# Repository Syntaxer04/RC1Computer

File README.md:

# RC1Computer
8-Bit Relay Computer inspired by Harry Porter and DipDot
# General Information
This Computer, inspired Harry H Porter III, Ph.D, Paul Law, and Youtuber DipDot, is (almost) completly made out of relays, 607 of them to be exact.

# Specifications
- 32 kb RAM
- It has ~11~ 15 8 Bit Registers. Some of them can also funtcion as 16 Bit Registers.
- A clock rate Between 3 and 8 Hertz
- 8 Bit Data and Instruction Bus, as well as an 16* Bit Adress Bus
<sub>*only 15 bits are actually used, but the 16th Bit is still usable for other Peripherals/More Memeory</sub>

# Changes in V0.2
- Changed how I managed the Bus on the RC-1. The Bus Board now encompasses all Register Signals and otherwise, except for the Timing pulses, which is only used by the Controller.
- Caught most the Routing mistakes I made in the first Version. The second run really helped spotting obvious and not so obvious mistakes.
- Added a board for the front panel functions. The switches are not mounted on the Board however, and so are the LEDs.
- I also started experimenting with Capacitor Storage. I included my initial design in this version.
- The memory board had an overhaul, with more isolation and better logic.
- The ALU has been split into two boards. I was able to do this because of the new backplane.

# Future features
- ~I want to make some sort Storage medium. A Tape interface, similar to DipDot's design, would be nice, although for a computer like that kind of lame in my opinion. I am thinking more like a paper based interface, like the one Usagi electric build for the [UE1](https://www.youtube.com/playlist?list=PLnw98JPyObn0v-98gRV9PfzAQONTKxql3). One Slight Problem thogh: _Reading_ may be somewhat easy, the _writing_ on the other hand may be a little challenge... We'll burn that bridge when we get there.~
- Tape Loader has been added, function not Tested however.
- The Second thing i want to make for this project is some sort of Serial/ Terminal output. That itself is not that hard all things considered, it's nearly a chip solution. The real problem is that the Computer most likely lacks any sort of speed for that kind of outpu. So i either have to buffer the output, make it _exceptionaly_ slow, or find some other way of sending a serial signal of of the Computer.

# Links
[Paul Law´s Youtube channel](https://www.youtube.com/@paul80nd), and his [personal Blog](https://www.relaycomputer.co.uk/).
[Harry Porter´s Webiste](https://web.cecs.pdx.edu/~harry/Relay/index.html), specifically, [this PDF](https://web.cecs.pdx.edu/~harry/Relay/RelayPaper.pdf).
Lastly, [DipDot´s Youtube channel](https://www.youtube.com/@dipdoting). He was the main inspiration for this project and his videos are well made.

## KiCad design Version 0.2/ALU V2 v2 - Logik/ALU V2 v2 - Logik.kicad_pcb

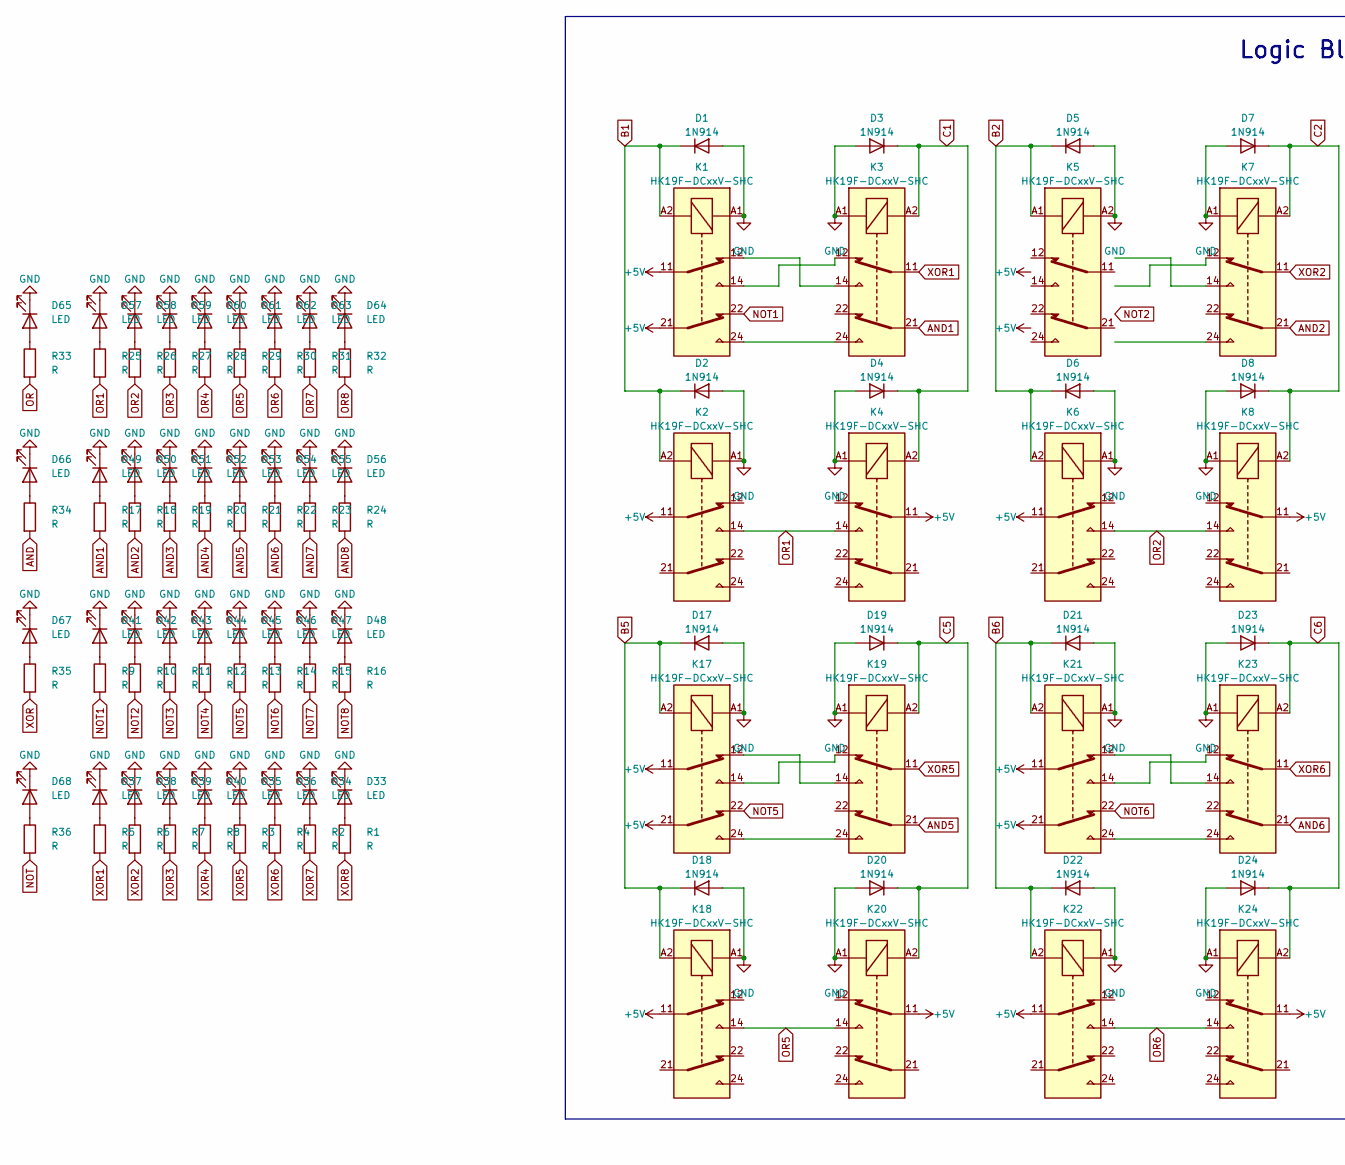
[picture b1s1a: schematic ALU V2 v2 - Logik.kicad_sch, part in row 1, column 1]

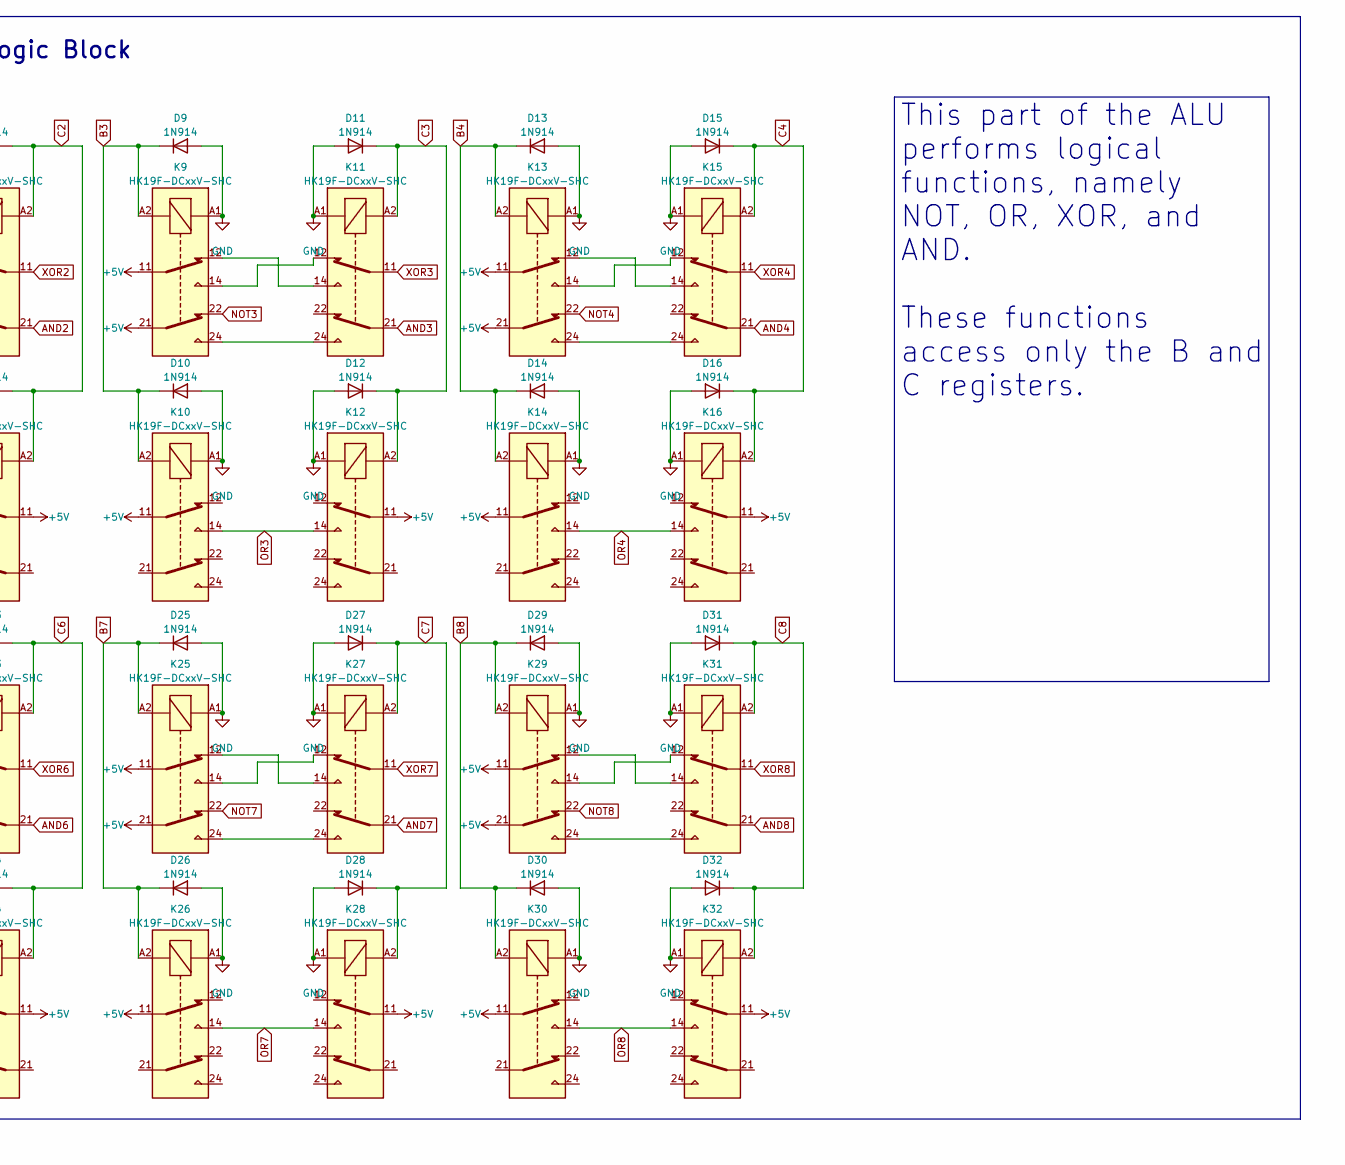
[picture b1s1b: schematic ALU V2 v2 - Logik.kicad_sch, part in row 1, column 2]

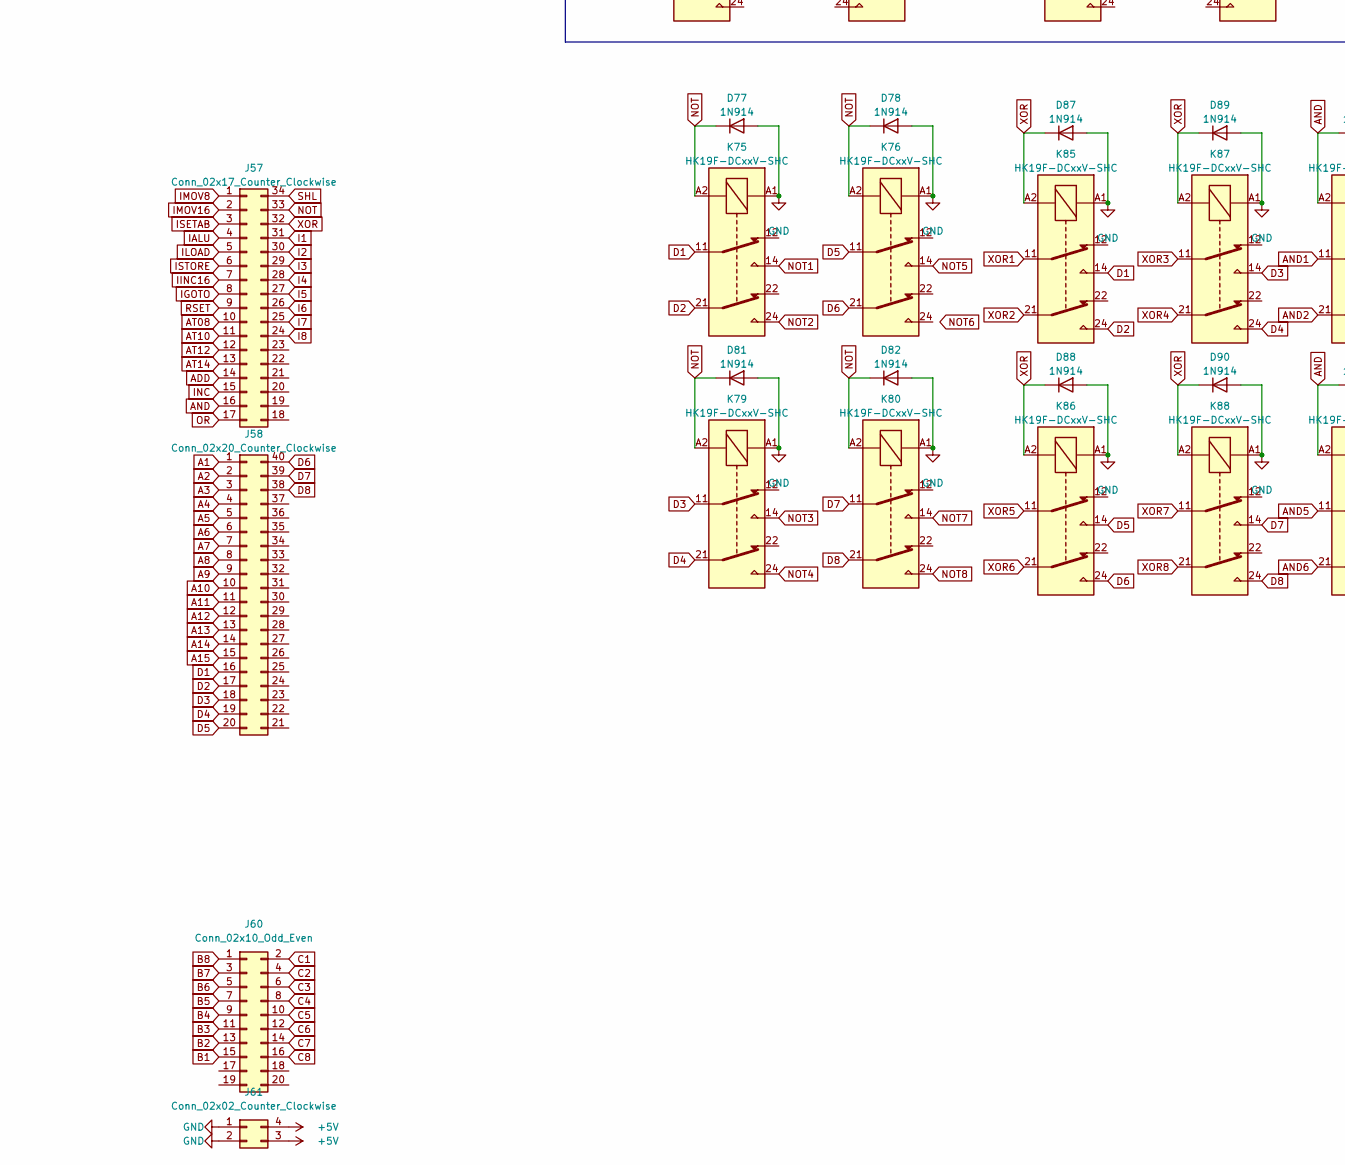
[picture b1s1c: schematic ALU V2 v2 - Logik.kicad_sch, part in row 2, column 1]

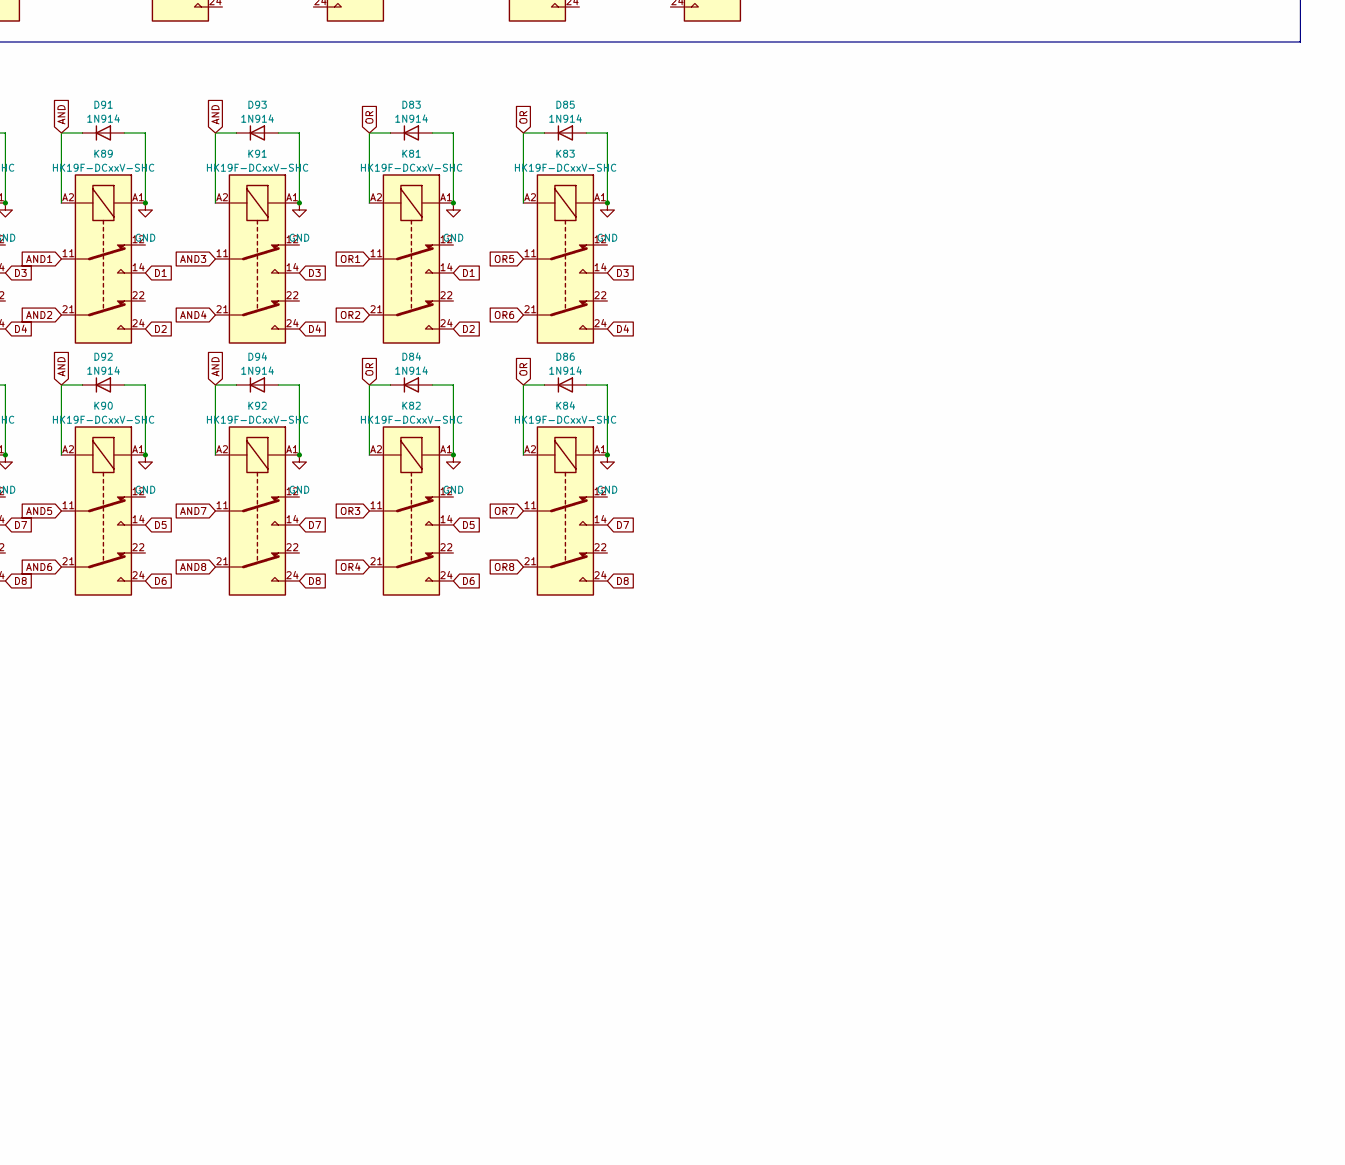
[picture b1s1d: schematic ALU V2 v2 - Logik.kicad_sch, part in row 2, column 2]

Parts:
D1, D2, D3, D4, D5, D6, D7, D8, D9, D10, D11, D12, D13, D14, D15, D16, D17, D18, D19, D20, D21, D22, D23, D24, D25, D26, D27, D28, D29, D30, D31, D32, D77, D78, D81, D82, D83, D84, D85, D86, D87, D88, D89, D90, D91, D92, D93, D94: 1N914; D_DO-35_SOD27_P7.62mm_Horizontal
D33, D34, D35, D36, D37, D38, D39, D40, D41, D42, D43, D44, D45, D46, D47, D48, D49, D50, D51, D52, D53, D54, D55, D56, D57, D58, D59, D60, D61, D62, D63, D64, D65, D66, D67, D68: LED; LED_D5.0mm
J57: Conn_02x17_Counter_Clockwise; PinSocket_2x17_P2.54mm_Horizontal
J58: Conn_02x20_Counter_Clockwise; PinSocket_2x20_P2.54mm_Horizontal
J60: Conn_02x10_Odd_Even; PinSocket_2x10_P2.54mm_Horizontal
J61: Conn_02x02_Counter_Clockwise; PinSocket_2x02_P2.54mm_Horizontal
K1, K2, K3, K4, K5, K6, K7, K8, K9, K10, K11, K12, K13, K14, K15, K16, K17, K18, K19, K20, K21, K22, K23, K24, K25, K26, K27, K28, K29, K30, K31, K32, K75, K76, K79, K80, K81, K82, K83, K84, K85, K86, K87, K88, K89, K90, K91, K92: HK19F-DCxxV-SHC; Relay_DPDT_Finder_30.22
R1, R2, R3, R4, R5, R6, R7, R8, R9, R10, R11, R12, R13, R14, R15, R16, R17, R18, R19, R20, R21, R22, R23, R24, R25, R26, R27, R28, R29, R30, R31, R32, R33, R34, R35, R36: R; R_Axial_DIN0309_L9.0mm_D3.2mm_P12.70mm_Horizontal

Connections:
+5V: J61.3, J61.4, K1.11, K1.21, K2.11, K4.11, K5.11, K5.21, K6.11, K8.11, K9.11, K9.21, K10.11, K12.11, K13.11, K13.21, K14.11, K16.11, K17.11, K17.21, K18.11, K20.11, K21.11, K21.21, K22.11, K24.11, K25.11, K25.21, K26.11, K28.11, K29.11, K29.21, K30.11, K32.11
A1: J58.1
A2: J58.2
A3: J58.3
A4: J58.4
A5: J58.5
A6: J58.6
A7: J58.7
A8: J58.8
A9: J58.9
A10: J58.10
A11: J58.11
A12: J58.12
A13: J58.13
A14: J58.14
A15: J58.15
ADD: J57.14
AND: D91.1 (K), D92.1 (K), D93.1 (K), D94.1 (K), J57.16, K89.A2, K90.A2, K91.A2, K92.A2, R34.2
AND1: K3.21, K89.11, R17.2
AND2: K7.21, K89.21, R18.2
AND3: K11.21, K91.11, R19.2
AND4: K15.21, K91.21, R20.2
AND5: K19.21, K90.11, R21.2
AND6: K23.21, K90.21, R22.2
AND7: K27.21, K92.11, R23.2
AND8: K31.21, K92.21, R24.2
AT08: J57.10
AT10: J57.11
AT12: J57.12
AT14: J57.13
B1: D1.1 (K), D2.1 (K), J60.15, K1.A2, K2.A2
B3: D9.1 (K), D10.1 (K), J60.11, K9.A2, K10.A2
B4: D13.1 (K), D14.1 (K), J60.9, K13.A2, K14.A2
B5: D17.1 (K), D18.1 (K), J60.7, K17.A2, K18.A2
B6: D21.1 (K), D22.1 (K), J60.5, K21.A2, K22.A2
B7: D25.1 (K), D26.1 (K), J60.3, K25.A2, K26.A2
B8: D29.1 (K), D30.1 (K), J60.1, K29.A2, K30.A2
C1: D3.1 (K), D4.1 (K), J60.2, K3.A2, K4.A2
C2: D7.1 (K), D8.1 (K), J60.4, K7.A2, K8.A2
C3: D11.1 (K), D12.1 (K), J60.6, K11.A2, K12.A2
C4: D15.1 (K), D16.1 (K), J60.8, K15.A2, K16.A2
C5: D19.1 (K), D20.1 (K), J60.10, K19.A2, K20.A2
C6: D23.1 (K), D24.1 (K), J60.12, K23.A2, K24.A2
C7: D27.1 (K), D28.1 (K), J60.14, K27.A2, K28.A2
C8: D31.1 (K), D32.1 (K), J60.16, K31.A2, K32.A2
D1: J58.16, K75.11, K81.14, K85.14, K89.14
D2: J58.17, K75.21, K81.24, K85.24, K89.24
D3: J58.18, K79.11, K83.14, K87.14, K91.14
D4: J58.19, K79.21, K83.24, K87.24, K91.24
D5: J58.20, K76.11, K82.14, K86.14, K90.14
D6: J58.40, K76.21, K82.24, K86.24, K90.24
D7: J58.39, K80.11, K84.14, K88.14, K92.14
D8: J58.38, K80.21, K84.24, K88.24, K92.24
I1: J57.31
I2: J57.30
I3: J57.29
I4: J57.28
I5: J57.27
I6: J57.26
I7: J57.25
I8: J57.24
IALU: J57.4
IGOTO: J57.8
IINC16: J57.7
ILOAD: J57.5
IMOV8: J57.1
IMOV16: J57.2
INC: J57.15
ISETAB: J57.3
ISTORE: J57.6
NOT: D77.1 (K), D78.1 (K), D81.1 (K), D82.1 (K), J57.33, K75.A2, K76.A2, K79.A2, K80.A2, R36.2
NOT1: K1.22, K75.14, R9.2
NOT2: K5.22, K75.24, R10.2
NOT3: K9.22, K79.14, R11.2
NOT4: K13.22, K79.24, R12.2
NOT5: K17.22, K76.14, R13.2
NOT6: K21.22, R14.2
NOT7: K25.22, K80.14, R15.2
NOT8: K29.22, K80.24, R16.2
unnamed: D33.2 (A), R1.1
unnamed: D34.2 (A), R2.1
unnamed: D35.2 (A), R3.1
unnamed: D36.2 (A), R4.1
unnamed: D37.2 (A), R5.1
unnamed: D38.2 (A), R6.1
unnamed: D39.2 (A), R7.1
unnamed: D40.2 (A), R8.1
unnamed: D41.2 (A), R9.1
unnamed: D42.2 (A), R10.1
unnamed: D43.2 (A), R11.1
unnamed: D44.2 (A), R12.1
unnamed: D45.2 (A), R13.1
unnamed: D46.2 (A), R14.1
unnamed: D47.2 (A), R15.1
unnamed: D48.2 (A), R16.1
unnamed: D49.2 (A), R17.1
unnamed: D50.2 (A), R18.1
unnamed: D51.2 (A), R19.1
unnamed: D52.2 (A), R20.1
unnamed: D53.2 (A), R21.1
unnamed: D54.2 (A), R22.1
unnamed: D55.2 (A), R23.1
unnamed: D56.2 (A), R24.1
unnamed: D57.2 (A), R25.1
unnamed: D58.2 (A), R26.1
unnamed: D59.2 (A), R27.1
unnamed: D60.2 (A), R28.1
unnamed: D61.2 (A), R29.1
unnamed: D62.2 (A), R30.1
unnamed: D63.2 (A), R31.1
unnamed: D64.2 (A), R32.1
unnamed: D65.2 (A), R33.1
unnamed: D66.2 (A), R34.1
unnamed: D67.2 (A), R35.1
unnamed: D68.2 (A), R36.1
unnamed: K1.12, K3.14
unnamed: K1.14, K3.12
unnamed: K1.24, K3.24
unnamed: K5.12, K7.14
unnamed: K5.14, K7.12
unnamed: K5.24, K7.24
unnamed: K9.14, K11.12
unnamed: K9.12, K11.14
unnamed: K9.24, K11.24
unnamed: K13.12, K15.14
unnamed: K13.14, K15.12
unnamed: K13.24, K15.24
unnamed: K17.12, K19.14
unnamed: K17.14, K19.12
unnamed: K17.24, K19.24
unnamed: K21.12, K23.14
unnamed: K21.14, K23.12
unnamed: K21.24, K23.24
unnamed: K25.12, K27.14
unnamed: K25.14, K27.12
unnamed: K25.24, K27.24
unnamed: K29.12, K31.14
unnamed: K29.14, K31.12
unnamed: K29.24, K31.24
OR: D83.1 (K), D84.1 (K), D85.1 (K), D86.1 (K), J57.17, K81.A2, K82.A2, K83.A2, K84.A2, R33.2
OR1: K2.14, K4.14, K81.11, R25.2
OR2: K6.14, K8.14, K81.21, R26.2
OR3: K10.14, K12.14, K82.11, R27.2
OR4: K14.14, K16.14, K82.21, R28.2
OR5: K18.14, K20.14, K83.11, R29.2
OR6: K22.14, K24.14, K83.21, R30.2
OR7: K26.14, K28.14, K84.11, R31.2
OR8: K30.14, K32.14, K84.21, R32.2
RSET: J57.9
SHL: J57.34
XOR: D87.1 (K), D88.1 (K), D89.1 (K), D90.1 (K), J57.32, K85.A2, K86.A2, K87.A2, K88.A2, R35.2
XOR1: K3.11, K85.11, R5.2
XOR2: K7.11, K85.21, R6.2
XOR3: K11.11, K87.11, R7.2
XOR4: K15.11, K87.21, R8.2
XOR5: K19.11, K86.11, R3.2
XOR6: K23.11, K86.21, R4.2
XOR7: K27.11, K88.11, R2.2
XOR8: K31.11, K88.21, R1.2

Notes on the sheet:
Logic Block
This part of the ALU performs logical functions, namely NOT, OR, XOR, and AND. These functions access only the B and C registers.

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
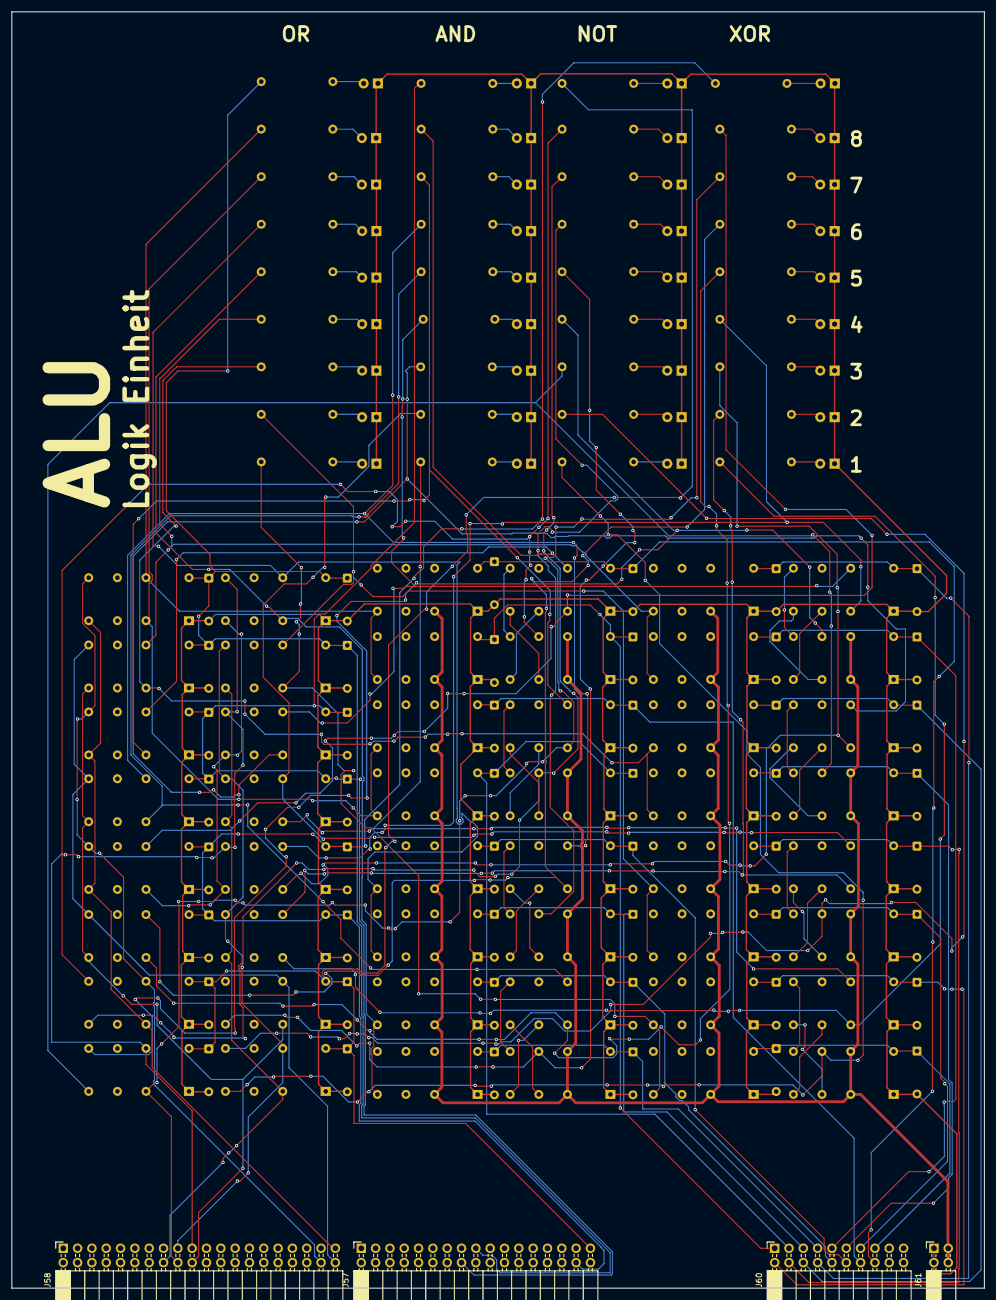
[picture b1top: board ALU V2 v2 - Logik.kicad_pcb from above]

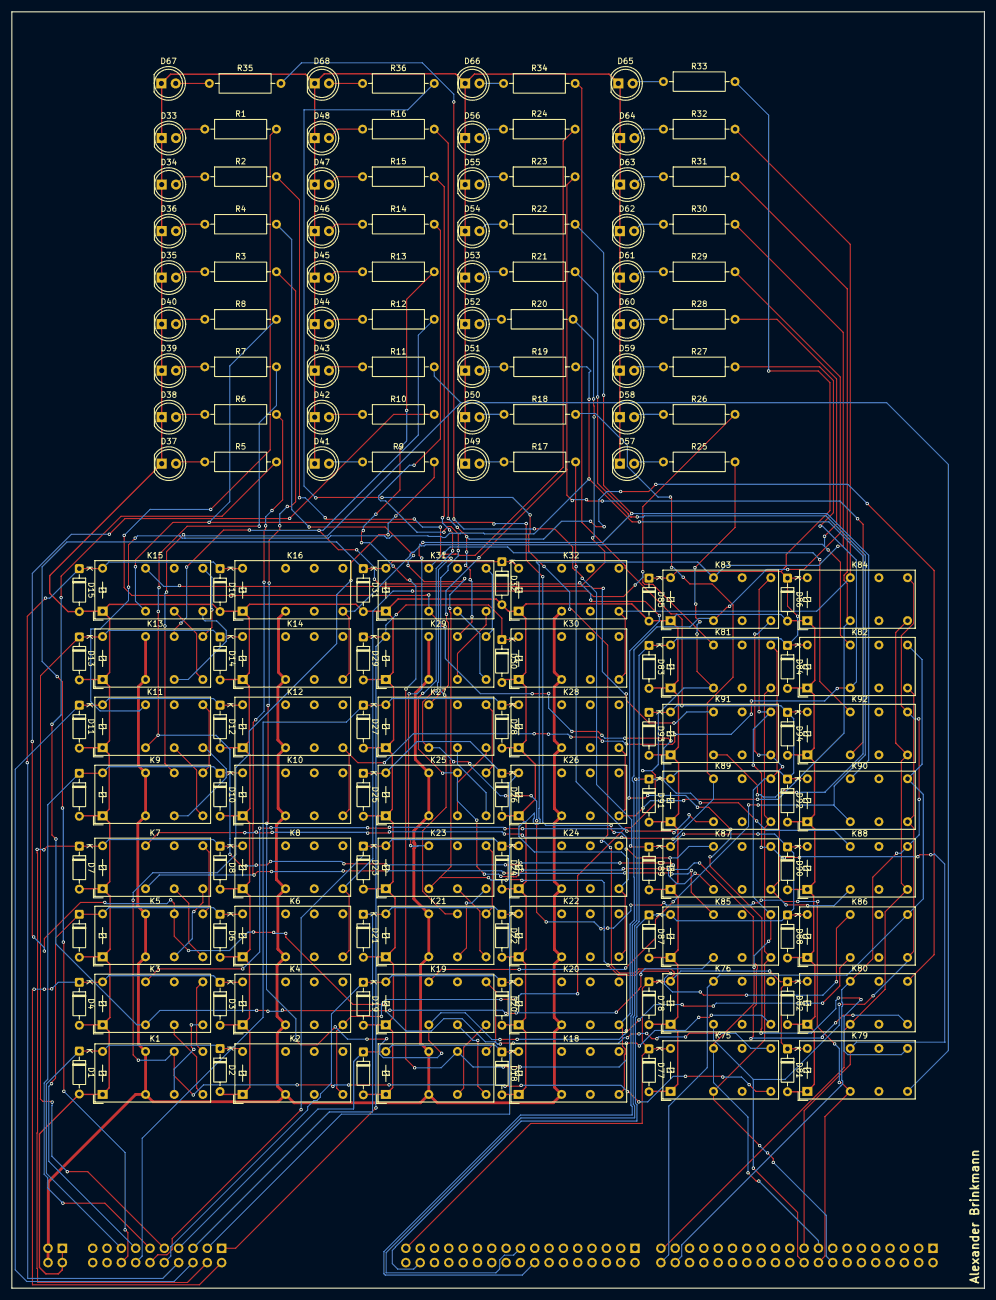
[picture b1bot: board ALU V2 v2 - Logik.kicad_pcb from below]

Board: 2 copper layers, 172.5 x 226.3 mm, 172 parts (168 on the bottom side), 122 nets.

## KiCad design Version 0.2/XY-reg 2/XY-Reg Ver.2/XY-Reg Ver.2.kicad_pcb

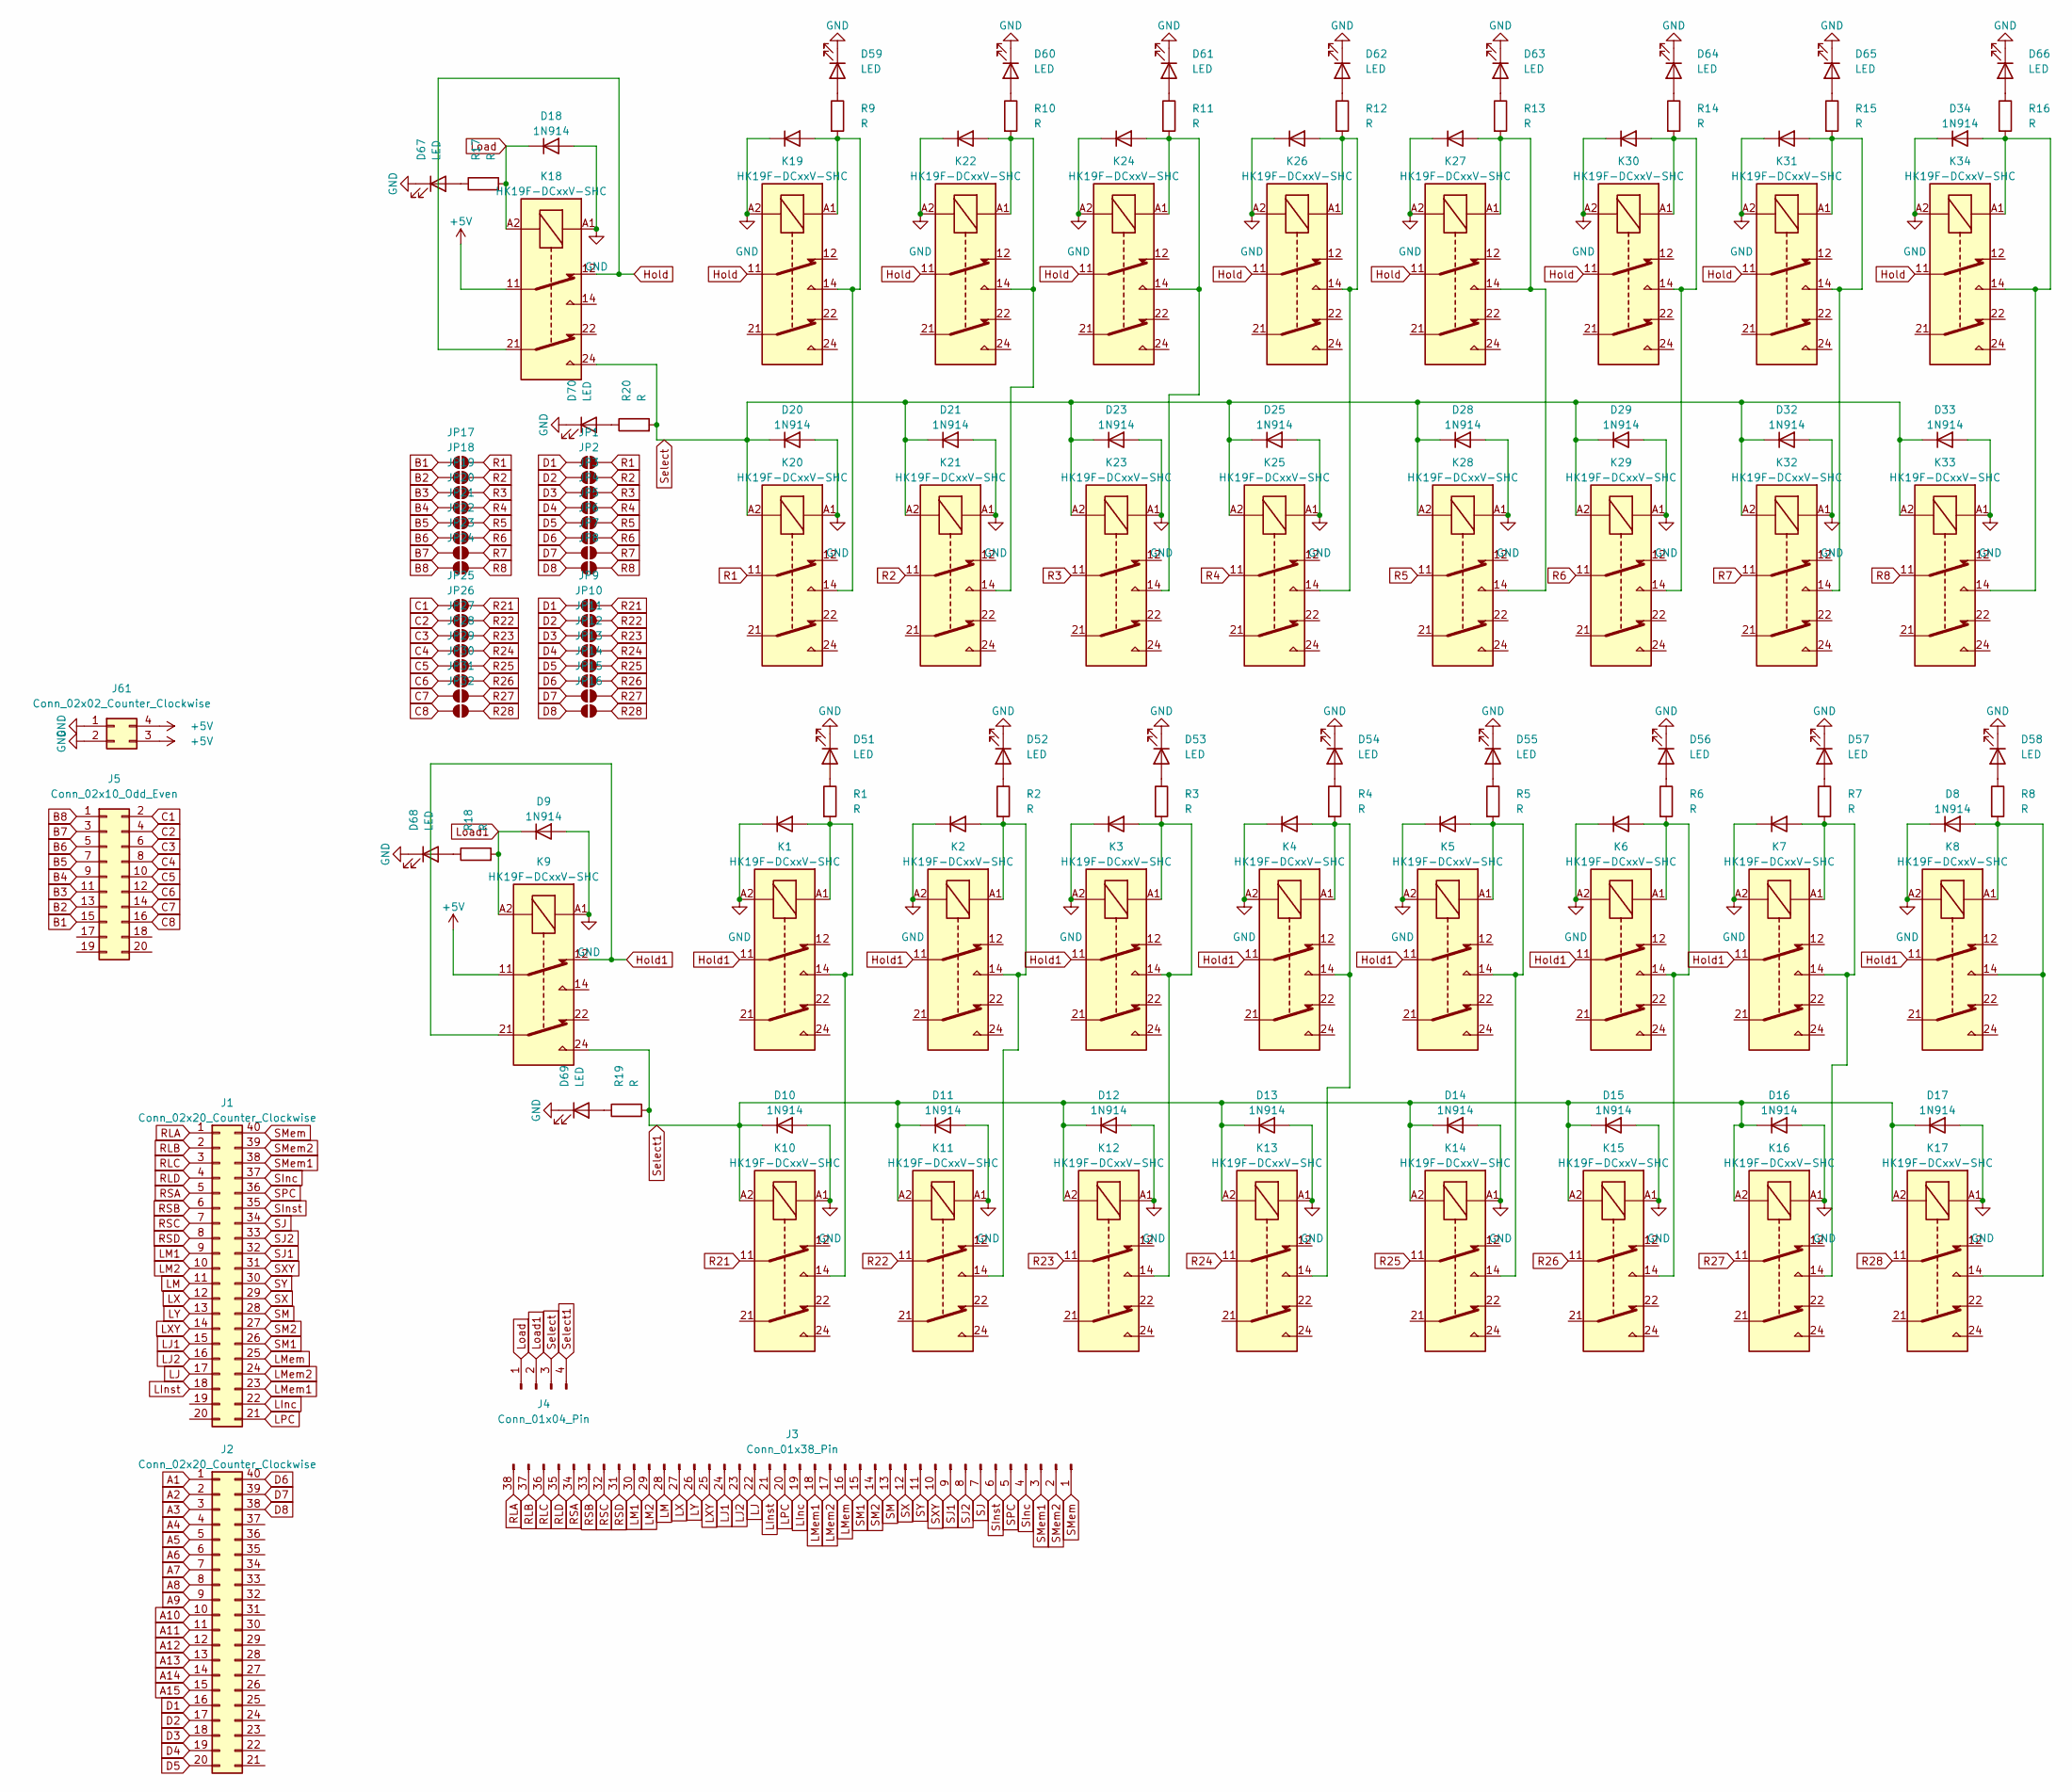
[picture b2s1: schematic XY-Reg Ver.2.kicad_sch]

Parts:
D1, D2, D3, D4, D5, D6, D7, D8, D9, D10, D11, D12, D13, D14, D15, D16, D17, D18, D19, D20, D21, D22, D23, D24, D25, D26, D27, D28, D29, D30, D31, D32, D33, D34: 1N914; D_DO-35_SOD27_P7.62mm_Horizontal
D51, D52, D53, D54, D55, D56, D57, D58, D59, D60, D61, D62, D63, D64, D65, D66, D67, D68, D70: LED; LED_D5.0mm ohne SilkS
D69: LED; LED_D5.0mm
J1, J2: Conn_02x20_Counter_Clockwise; PinSocket_2x20_P2.54mm_Horizontal
J3: Conn_01x38_Pin; PinHeader_1x38_P2.54mm_Vertical
J4: Conn_01x04_Pin; PinHeader_1x04_P2.54mm_Vertical
J5: Conn_02x10_Odd_Even; PinHeader_2x10_P2.54mm_Horizontal
J61: Conn_02x02_Counter_Clockwise; PinSocket_2x02_P2.54mm_Vertical
JP1, JP2, JP3, JP4, JP5, JP6, JP7, JP8, JP9, JP10, JP11, JP12, JP13, JP14, JP15, JP16, JP17, JP18, JP19, JP20, JP21, JP22, JP23, JP24, JP25, JP26, JP27, JP28, JP29, JP30, JP31, JP32: SolderJumper_2_Open; SolderJumper-2_P1.3mm_Open_Pad1.0x1.5mm
K1, K2, K3, K4, K5, K6, K7, K8, K9, K10, K11, K12, K13, K14, K15, K16, K17, K18, K19, K20, K21, K22, K23, K24, K25, K26, K27, K28, K29, K30, K31, K32, K33, K34: HK19F-DCxxV-SHC; Relay_DPDT_Finder_30.22 ohne SilkS
R1, R2, R3, R4, R5, R6, R7, R8, R9, R10, R11, R12, R13, R14, R15, R16, R17, R18, R19, R20: R; R_Axial_DIN0204_L3.6mm_D1.6mm_P7.62mm_Horizontal

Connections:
+5V: J61.3, J61.4, K9.11, K18.11
A1: J2.1
A2: J2.2
A3: J2.3
A4: J2.4
A5: J2.5
A6: J2.6
A7: J2.7
A8: J2.8
A9: J2.9
A10: J2.10
A11: J2.11
A12: J2.12
A13: J2.13
A14: J2.14
A15: J2.15
B1: J5.15, JP17.1 (A)
B2: J5.13, JP18.1 (A)
B3: J5.11, JP19.1 (A)
B4: J5.9, JP20.1 (A)
B5: J5.7, JP21.1 (A)
B6: J5.5, JP22.1 (A)
B7: J5.3, JP23.1 (A)
B8: J5.1, JP24.1 (A)
C1: J5.2, JP25.1 (A)
C2: J5.4, JP26.1 (A)
C3: J5.6, JP27.1 (A)
C4: J5.8, JP28.1 (A)
C5: J5.10, JP29.1 (A)
C6: J5.12, JP30.1 (A)
C7: J5.14, JP31.1 (A)
C8: J5.16, JP32.1 (A)
D1: J2.16, JP1.1 (A), JP9.1 (A)
D2: J2.17, JP2.1 (A), JP10.1 (A)
D3: J2.18, JP3.1 (A), JP11.1 (A)
D4: J2.19, JP4.1 (A), JP12.1 (A)
D5: J2.20, JP5.1 (A), JP13.1 (A)
D6: J2.40, JP6.1 (A), JP14.1 (A)
D7: J2.39, JP7.1 (A), JP15.1 (A)
D8: J2.38, JP8.1 (A), JP16.1 (A)
GND: D1.1 (K), D2.1 (K), D3.1 (K), D4.1 (K), D5.1 (K), D6.1 (K), D7.1 (K), D8.1 (K), D9.2 (A), D10.2 (A), D11.2 (A), D12.2 (A), D13.2 (A), D14.2 (A), D15.2 (A), D16.2 (A), D17.2 (A), D18.2 (A), D19.1 (K), D20.2 (A), D21.2 (A), D22.1 (K), D23.2 (A), D24.1 (K), D25.2 (A), D26.1 (K), D27.1 (K), D28.2 (A), D29.2 (A), D30.1 (K), D31.1 (K), D32.2 (A), D33.2 (A), D34.1 (K), D51.1 (K), D52.1 (K), D53.1 (K), D54.1 (K), D55.1 (K), D56.1 (K), D57.1 (K), D58.1 (K), D59.1 (K), D60.1 (K), D61.1 (K), D62.1 (K), D63.1 (K), D64.1 (K), D65.1 (K), D66.1 (K), D67.1 (K), D68.1 (K), D69.1 (K), D70.1 (K), J61.1, J61.2, K1.A2, K2.A2, K3.A2, K4.A2, K5.A2, K6.A2, K7.A2, K8.A2, K9.A1, K10.A1, K11.A1, K12.A1, K13.A1, K14.A1, K15.A1, K16.A1, K17.A1, K18.A1, K19.A2, K20.A1, K21.A1, K22.A2, K23.A1, K24.A2, K25.A1, K26.A2, K27.A2, K28.A1, K29.A1, K30.A2, K31.A2, K32.A1, K33.A1, K34.A2
Hold: K18.12, K18.21, K19.11, K22.11, K24.11, K26.11, K27.11, K30.11, K31.11, K34.11
Hold1: K1.11, K2.11, K3.11, K4.11, K5.11, K6.11, K7.11, K8.11, K9.12, K9.21
LInc: J1.22, J3.19
LInst: J1.18, J3.21
LJ1: J1.15, J3.24
LJ2: J1.16, J3.23
LJ: J1.17, J3.22
LM: J1.11, J3.28
LM1: J1.9, J3.30
LM2: J1.10, J3.29
LMem: J1.25, J3.16
LMem1: J1.23, J3.18
LMem2: J1.24, J3.17
LPC: J1.21, J3.20
LX: J1.12, J3.27
LXY: J1.14, J3.25
LY: J1.13, J3.26
Load: D18.1 (K), J4.1, K18.A2, R17.2
Load1: D9.1 (K), J4.2, K9.A2, R18.2
unnamed: D1.2 (A), K1.14, K1.A1, K10.14, R1.2
unnamed: D2.2 (A), K2.14, K2.A1, K11.14, R2.2
unnamed: D3.2 (A), K3.14, K3.A1, K12.14, R3.2
unnamed: D4.2 (A), K4.14, K4.A1, K13.14, R4.2
unnamed: D5.2 (A), K5.14, K5.A1, K14.14, R5.2
unnamed: D6.2 (A), K6.14, K6.A1, K15.14, R6.2
unnamed: D7.2 (A), K7.14, K7.A1, K16.14, R7.2
unnamed: D8.2 (A), K8.14, K8.A1, K17.14, R8.2
unnamed: D19.2 (A), K19.14, K19.A1, K20.14, R9.2
unnamed: D22.2 (A), K21.14, K22.14, K22.A1, R10.2
unnamed: D24.2 (A), K23.14, K24.14, K24.A1, R11.2
unnamed: D26.2 (A), K25.14, K26.14, K26.A1, R12.2
unnamed: D27.2 (A), K27.14, K27.A1, K28.14, R13.2
unnamed: D30.2 (A), K29.14, K30.14, K30.A1, R14.2
unnamed: D31.2 (A), K31.14, K31.A1, K32.14, R15.2
unnamed: D34.2 (A), K33.14, K34.14, K34.A1, R16.2
unnamed: D51.2 (A), R1.1
unnamed: D52.2 (A), R2.1
unnamed: D53.2 (A), R3.1
unnamed: D54.2 (A), R4.1
unnamed: D55.2 (A), R5.1
unnamed: D56.2 (A), R6.1
unnamed: D57.2 (A), R7.1
unnamed: D58.2 (A), R8.1
unnamed: D59.2 (A), R9.1
unnamed: D60.2 (A), R10.1
unnamed: D61.2 (A), R11.1
unnamed: D62.2 (A), R12.1
unnamed: D63.2 (A), R13.1
unnamed: D64.2 (A), R14.1
unnamed: D65.2 (A), R15.1
unnamed: D66.2 (A), R16.1
unnamed: D67.2 (A), R17.1
unnamed: D68.2 (A), R18.1
unnamed: D69.2 (A), R19.1
unnamed: D70.2 (A), R20.1
R1: JP1.2 (B), JP17.2 (B), K20.11
R2: JP2.2 (B), JP18.2 (B), K21.11
R3: JP3.2 (B), JP19.2 (B), K23.11
R4: JP4.2 (B), JP20.2 (B), K25.11
R5: JP5.2 (B), JP21.2 (B), K28.11
R6: JP6.2 (B), JP22.2 (B), K29.11
R7: JP7.2 (B), JP23.2 (B), K32.11
R8: JP8.2 (B), JP24.2 (B), K33.11
R21: JP9.2 (B), JP25.2 (B), K10.11
R22: JP10.2 (B), JP26.2 (B), K11.11
R23: JP11.2 (B), JP27.2 (B), K12.11
R24: JP12.2 (B), JP28.2 (B), K13.11
R25: JP13.2 (B), JP29.2 (B), K14.11
R26: JP14.2 (B), JP30.2 (B), K15.11
R27: JP15.2 (B), JP31.2 (B), K16.11
R28: JP16.2 (B), JP32.2 (B), K17.11
RLA: J1.1, J3.38
RLB: J1.2, J3.37
RLC: J1.3, J3.36
RLD: J1.4, J3.35
RSA: J1.5, J3.34
RSB: J1.6, J3.33
RSC: J1.7, J3.32
RSD: J1.8, J3.31
SInc: J1.37, J3.4
SInst: J1.35, J3.6
SJ1: J1.32, J3.9
SJ2: J1.33, J3.8
SJ: J1.34, J3.7
SM: J1.28, J3.13
SM1: J1.26, J3.15
SM2: J1.27, J3.14
SMem: J1.40, J3.1
SMem1: J1.38, J3.3
SMem2: J1.39, J3.2
SPC: J1.36, J3.5
SX: J1.29, J3.12
SXY: J1.31, J3.10
SY: J1.30, J3.11
Select: D20.1 (K), D21.1 (K), D23.1 (K), D25.1 (K), D28.1 (K), D29.1 (K), D32.1 (K), D33.1 (K), J4.3, K18.24, K20.A2, K21.A2, K23.A2, K25.A2, K28.A2, K29.A2, K32.A2, K33.A2, R20.2
Select1: D10.1 (K), D11.1 (K), D12.1 (K), D13.1 (K), D14.1 (K), D15.1 (K), D16.1 (K), D17.1 (K), J4.4, K9.24, K10.A2, K11.A2, K12.A2, K13.A2, K14.A2, K15.A2, K16.A2, K17.A2, R19.2
